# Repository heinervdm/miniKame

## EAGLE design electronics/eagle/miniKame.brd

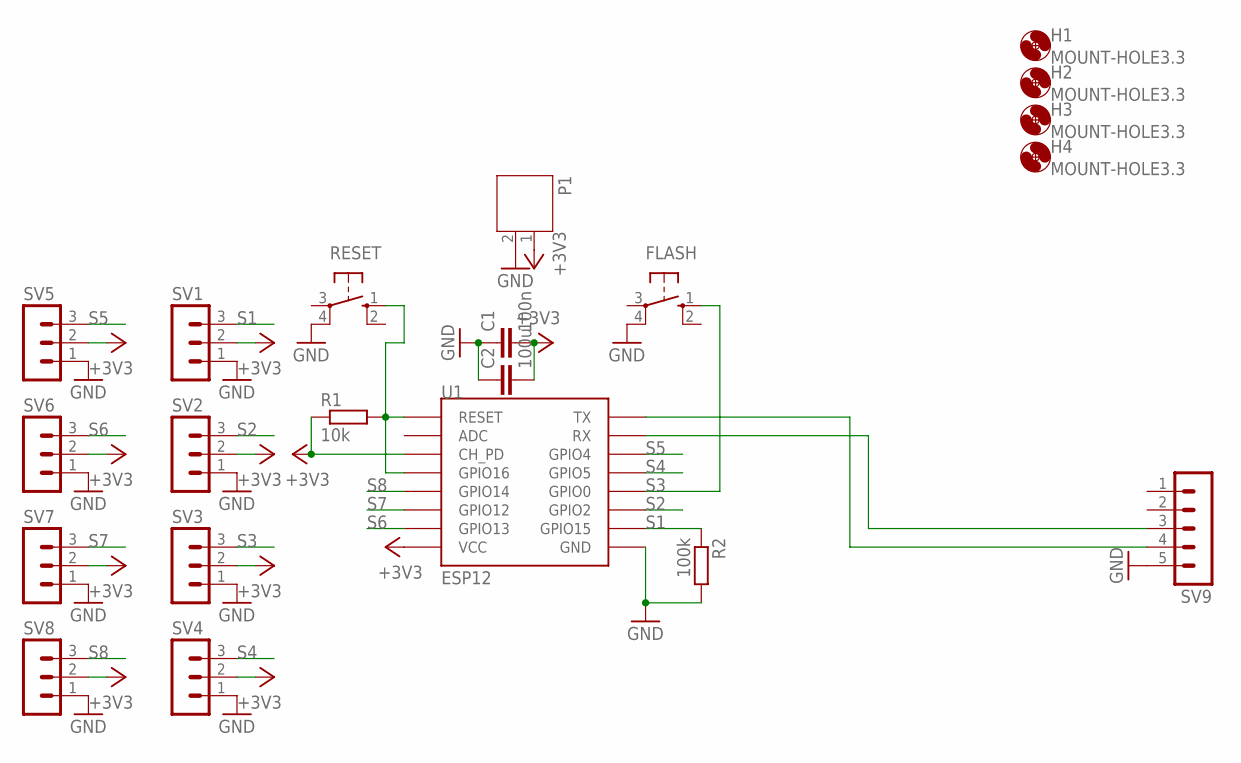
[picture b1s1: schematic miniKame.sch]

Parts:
C1: 100n; C0805
C2: 100u; C0805
FLASH: 10-XX; B3F-10XX
H1, H2, H3, H4: MOUNT-HOLE3.3; 3,3
P1: JST-PH2
R1: 10k; M0805
R2: 100k; M0805
RESET: 10-XX; B3F-10XX
SV1, SV2, SV3, SV4, SV5, SV6, SV7, SV8: MA03-1
SV9: MA05-1
U1: ESP12

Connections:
+3V3: C1.2, C2.2, P1.1, R1.1, SV1.2, SV2.2, SV3.2, SV4.2, SV5.2, SV6.2, SV7.2, SV8.2, U1.CH_PD, U1.VCC
GND: C1.1, C2.1, FLASH.4 (P1), P1.2, R2.2, RESET.4 (P1), SV1.1, SV2.1, SV3.1, SV4.1, SV5.1, SV6.1, SV7.1, SV8.1, SV9.5, U1.GND
unnamed: SV9.4, U1.TX
unnamed: SV9.3, U1.RX
unnamed: R1.2, RESET.1 (S), U1.GPIO16, U1.RESET
S1: R2.1, SV1.3, U1.GPIO15
S2: SV2.3, U1.GPIO2
S3: FLASH.1 (S), SV3.3, U1.GPIO0
S4: SV4.3, U1.GPIO5
S5: SV5.3, U1.GPIO4
S6: SV6.3, U1.GPIO13
S7: SV7.3, U1.GPIO12
S8: SV8.3, U1.GPIO14

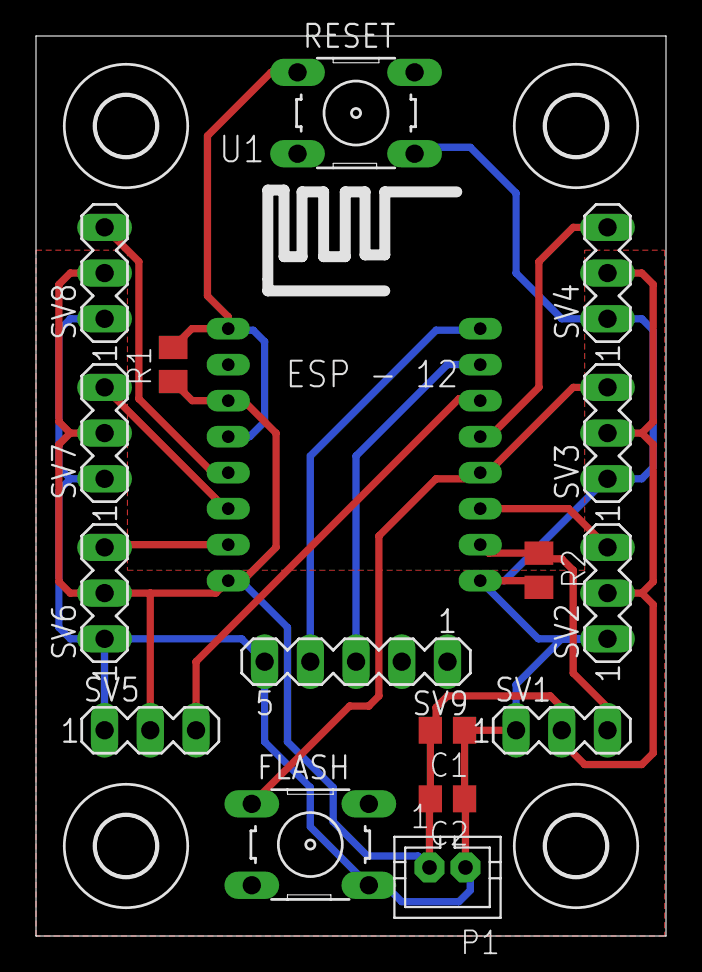
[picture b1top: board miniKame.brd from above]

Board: 2 copper layers, 35.0 x 50.0 mm, 21 parts (0 on the bottom side), 13 nets.

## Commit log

2016-03-28 Add esp-sdk version
2016-04-24 Add modified brackets
2016-04-24 remove gpio.h includes
2016-04-24 Add modified body from https://github.com/owenlab/poorkame
2016-04-24 Make brackets fit better
2016-04-24 Add .gitignore for esp-nonos-sdk
2016-04-24 Add initial TCP server code
2016-04-24 Make it compile
2016-04-25 Add initial version of a PCB, not yet finished
2016-04-25 update PCB
2016-05-01 modify leg parts to better fit SG90 servo horns
2016-05-01 Add bodyB with larger screwholes, my printer prints them to small
2016-05-06 update servohorn size of brackets
2016-10-06 Rebuild leftLegB completly in openSCAD
2016-10-06 update eagle project file
2016-10-08 Add modfied Body which should fit tower pro sg90 servos
2016-10-08 Also add stl
2016-10-09 Fix BodyA
